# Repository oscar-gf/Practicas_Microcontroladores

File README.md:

# # Microcontroller Laboratory

## Introduction

Microcontrollers are all around  he world. Each day, Microcontrollers, are more present in the many aspects of our lives: in our work, inside our houses, and in more. We can find them controlling small devices like cellphones, microwaves, washing machines, and televisions.

A microcontroller is one device or chip that is used to govern one or more processes. For example, the controller that regulates the room temperature of an air conditioner; it has a sensor that continuously measures the internal temperature and, when the preset limits are exceeded, it generates the necessary signals to adjust the temperature.

## State of the Art

### The practices and the PIC microcontroller

The main objective of this practices is to provide students the foundation to fully understand the operation of the PIC18F45K50 microcontroller. This will be achieved through 11 documents that will guide the reader to create their own electronic card or Printed Circuit Board (PCB) and to be able to program it; in order to, execute different functions.

The advantages of ta PIC microcontroller to others on the market, which is why it will be used throughout this manual, are as follows:

- Easy to operate.
- There is enough documentation to work with it and it’s easy to obtain it.
- The price is comparatively lower than its competitors.
- It has a high operating speed.
- Development tools are cheap and easy to use.
- There are a variety of hardware that can record, erase and check the behavior of PIC.
- Once you learn to handle a PIC, it will easier to handle any other models of microcontrollers.

### KiCad EDA Software

KiCad is an open source software suite for Electronic Design Automation (EDA). The programs handle Schematic Capture,
and PCB Layout with Gerber output. The suite runs on Windows, Linux and macOS and is licensed under GNU GPL v3. The
first release date was in 1992 by its original author, Jean-Pierre Charras, but is now currently under development by
the KiCad Developers Team.

## Evaluation

- Demonstation  ... 60%
- Report .......... 40%

## Submission

Every submission must be in your own github repository. If you which you could fork this as skeleton. All pull request
will be denied.

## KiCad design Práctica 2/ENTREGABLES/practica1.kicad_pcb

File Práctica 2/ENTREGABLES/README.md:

### Report
For this practice, modify only the Conclusion section. Commit an push the changes on the fork of this repository and add
upload the link on Canvas.

### File uploads
Commit and push the files with extensions .pro and .kicad_pcb created once you completed all the steps of the document in the repository.

### Demonstration
Screenshot the image of the complete schematic and upload it at the repository.

```diff
+ PCB - Complete Schematic
```

## Conclusion

El software es muy interesante pero no te hace las cosas fáciles, debido que, al momento de crear nuestra placa, descubres que todos los componentes eléctricos que insertamos en el esquematico los importa al PCB agrupados, por lo que hace un poco difícil las cosas. Sin embargo, como diseñadores de la placa nos ayuda a identificar cada pieza y por ende el comenzar a diseñar el cómo vamos a distribuir las piezas alrededor de la placa de la mejor manera

Al principio era algo complicado, pero con el video proporcionado por el instructor y la sesión de dudas que tuvimos todo comenzó a fluir en gran medida. Por último, en las últimas conexiones no entendía lo que me indicaba o por qué el software quería conectar un cable donde no iba asignado, según las imágenes predispuestas. Sin embargo, al hacer zoom en la placa las mismas líneas te revelan más información. En este caso ,había ignorado el ground de ciertos componentes por lo que esas líneas faltantes buscaban un ground común y detectaban que habia un ground en la placa yy te hacía la sugerencia de donde lo podias conectar. Gracias a ello entendí que una de las líneas del diseño de la placa era una tierra general para todos los componentes de la placa.

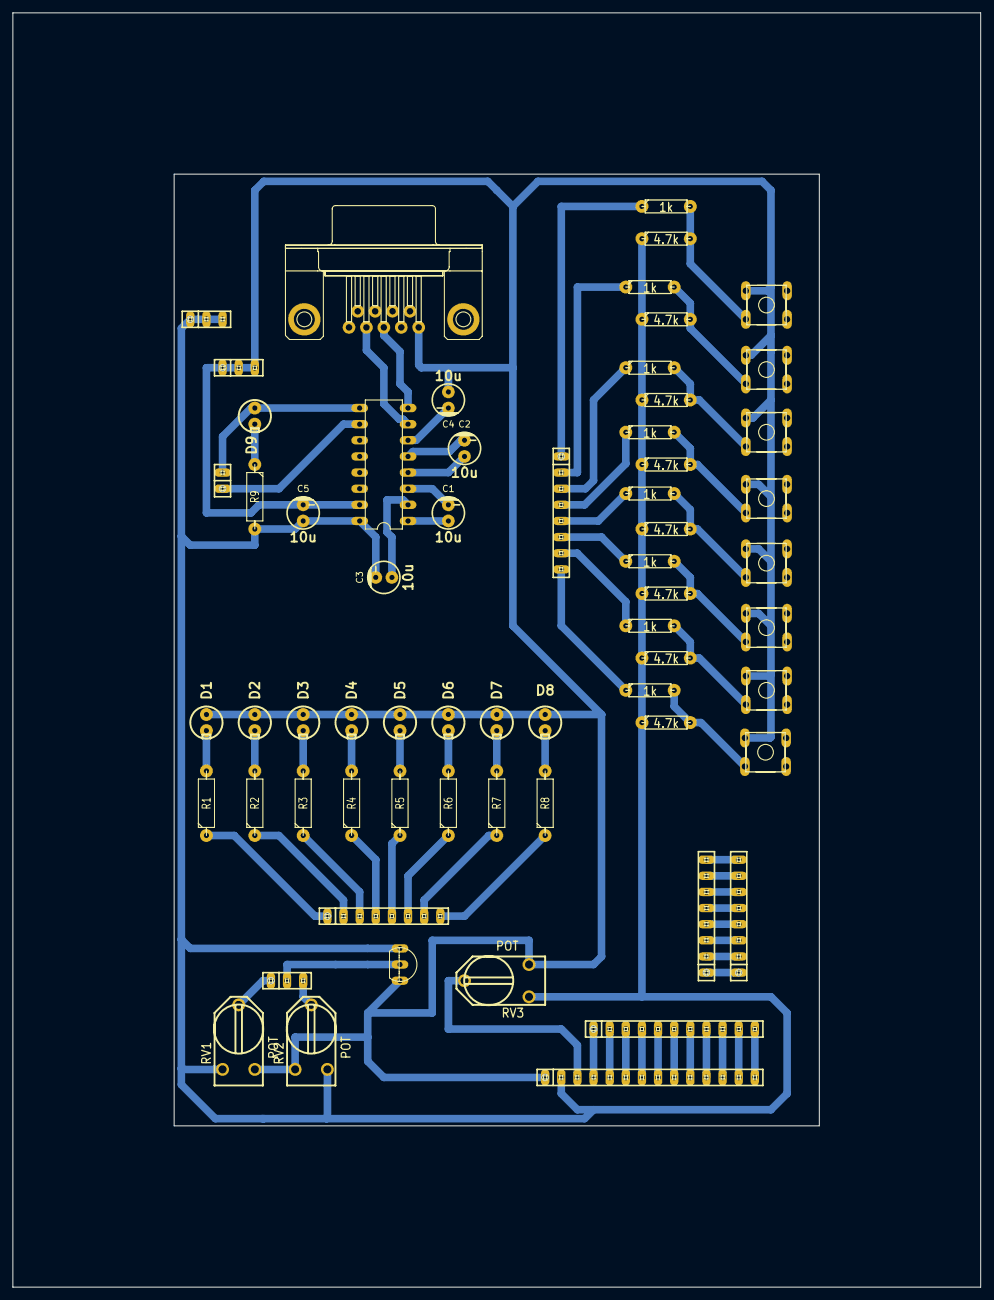
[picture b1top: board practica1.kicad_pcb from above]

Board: 2 copper layers, 152.4 x 200.7 mm, 63 parts (0 on the bottom side), 68 nets.

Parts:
C1, C2, C3, C4, C5: 10u; Capacitor_elect
D1, D2, D3, D4, D5, D6, D7, D8, D9: LED; Led
JP1, JP2, JP4: PINHD-1X3; pinhead-1X03
JP3, JP5, JP6, JP10: PINHD-1X8; pinhead-1X08
JP7: PINHD-1X14; pinhead-1X14
JP8: PINHD-1X11; pinhead-1X11
JP9: PINHD-1X2; pinhead-1X02
R1, R2, R3, R4, R5, R6, R7, R8, R9: 470; Resistor_large
R10, R11, R12, R13, R14, R15, R16, R17: 1k; Resistor
R18, R19, R20, R21, R22, R23, R24, R25: 4.7k; Resistor
RV1, RV2, RV3: POT; RV2X4
S1, S2, S3, S4, S5, S6, S7, S8: DTS-6
U1: MCP9700A
U2: MAX232; Maxim232
X1: F09HP; Conector_F09HP

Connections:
+5VA: C3.2, C5.1, JP1.1, JP1.2, JP1.3, JP7.2, R9.2, R18.1, R19.1, R20.1, R21.1, R22.1, R23.1, R24.1, R25.1, RV1.1, RV2.3, RV3.1, U1.1, U2.16
GNDA: C4.1, C5.2, D1.1, D2.1, D3.1, D4.1, D5.1, D6.1, D7.1, D8.1, JP2.1, JP2.2, JP2.3, JP7.1, RV1.3, RV2.1, RV3.3, S1.1, S2.1, S3.1, S4.1, S5.1, S6.1, S7.1, S8.1, U1.3, U2.15, X1.5
unnamed: C1.1, U2.1
unnamed: C1.2, U2.3
unnamed: C2.1, U2.4
unnamed: C2.2, U2.5
unnamed: C3.1, U2.2
unnamed: C4.2, U2.6
unnamed: D1.2, R1.2
unnamed: D2.2, R2.2
unnamed: D3.2, R3.2
unnamed: D4.2, R4.2
unnamed: D5.2, R5.2
unnamed: D6.2, R6.2
unnamed: D7.2, R7.2
unnamed: D8.2, R8.2
unnamed: D9.1, JP9.2, U2.9
unnamed: D9.2, R9.1
unnamed: JP3.1, R1.1
unnamed: JP3.2, R2.1
unnamed: JP3.3, R3.1
unnamed: JP3.4, R4.1
unnamed: JP3.5, R5.1
unnamed: JP3.6, R6.1
unnamed: JP3.7, R7.1
unnamed: JP3.8, R8.1
unnamed: JP4.1, RV1.2
unnamed: JP4.2, U1.2
unnamed: JP4.3, RV2.2
unnamed: JP5.1, JP6.1
unnamed: JP5.2, JP6.2
unnamed: JP5.3, JP6.3
unnamed: JP5.4, JP6.4
unnamed: JP5.5, JP6.5
unnamed: JP5.6, JP6.6
unnamed: JP5.7, JP6.7
unnamed: JP5.8, JP6.8
unnamed: JP7.3, RV3.2
unnamed: JP7.4, JP8.1
unnamed: JP7.5, JP8.2
unnamed: JP7.6, JP8.3
unnamed: JP7.7, JP8.4
unnamed: JP7.8, JP8.5
unnamed: JP7.9, JP8.6
unnamed: JP7.10, JP8.7
unnamed: JP7.11, JP8.8
unnamed: JP7.12, JP8.9
unnamed: JP7.13, JP8.10
unnamed: JP7.14, JP8.11
unnamed: JP9.1, U2.10
unnamed: JP10.1, R10.1
unnamed: JP10.2, R11.1
unnamed: JP10.3, R12.1
unnamed: JP10.4, R13.1
unnamed: JP10.5, R14.1
unnamed: JP10.6, R15.1
unnamed: JP10.7, R16.1
unnamed: JP10.8, R17.1
unnamed: R10.2, R18.2, S1.3
unnamed: R11.2, R19.2, S2.3
unnamed: R12.2, R20.2, S3.3
unnamed: R13.2, R21.2, S4.3
unnamed: R14.2, R22.2, S5.3
unnamed: R15.2, R23.2, S6.3
unnamed: R16.2, R24.2, S7.3
unnamed: R17.2, R25.2, S8.3
unnamed: U2.7, X1.2
unnamed: U2.8, X1.3

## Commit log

2020-08-25 Instrucciones Práctica 1
2020-08-25 Add Practice 1 Instruccions
2020-08-25 Add files
